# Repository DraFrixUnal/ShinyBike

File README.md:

# Shiny Bike

Dispositivo que busca iluminar y señalizar a las bicicletas.

## Descripcion

Este dispositivo busca que los ciclistas puedan señalizar a traves de luces su recorrido en las calles (direccionales, frenado, parqueo). El dispositivo se divide en dos partes, la primera la cual es un control remoto permite al usuario emitir comandos manueales y comandos automaticos para el seña.amiento, segun que comando dicte se enviaran datos via Bluetooth a la segunda parte, la cual se encarga de iluminar los led RGB Ws2812b.

## Objetivos

- Desarrollar un dispositivo que sea capaz de iluminar y señalizar de forma remota a cualquier bicicleta.
- Desarrollar los esquematicos, PCB, diseños y codigos que permitan alcanzar el dispositivo y un buen aprendizaje

## Alcance

Todos los ciclistas que quieran iluminar sus aventuras en la calle.

## Planeación 

### Diagrama de Flujo

Aqui se establecio oficialmente las funciones y las interacciones del dispositivo.

### Diagrama de Cajas Negras

Aqui se establecieron las principales tecnologias.

# Diseño

En esta sección, se empieza diseñar y construir la parte electronica del dispositivo, con lo cual se diseñaron los esquematicos y las PCB.

## Esquematicos

Esquematico Control Remoto

Esquematico Luces

## PCB

PCB del Control Remoto

PCB de apartado de Luces

# Prueba y Trabajo hecho

Aqui se realizaron pruebas en ProtoBoard para corroborar el funcionamiento del codigo y construir el dispositivo final.

## Videos

Links de los videos:
 - Dispositivo funcionamiento [Vdf](https://youtu.be/l_CRdRnh4ok)
 - Explicacion Bluetooth [Veb](https://youtu.be/JUIpYABRpQY)
 - Videos de los problemas [Vp1](https://youtu.be/4-EyFK3v-QM),[Vp2](https://youtube.com/shorts/PcfQB73DB2A?feature=share),[Vp3](https://youtu.be/3R93eb1QBnk)

## Muchas gracias por su visita

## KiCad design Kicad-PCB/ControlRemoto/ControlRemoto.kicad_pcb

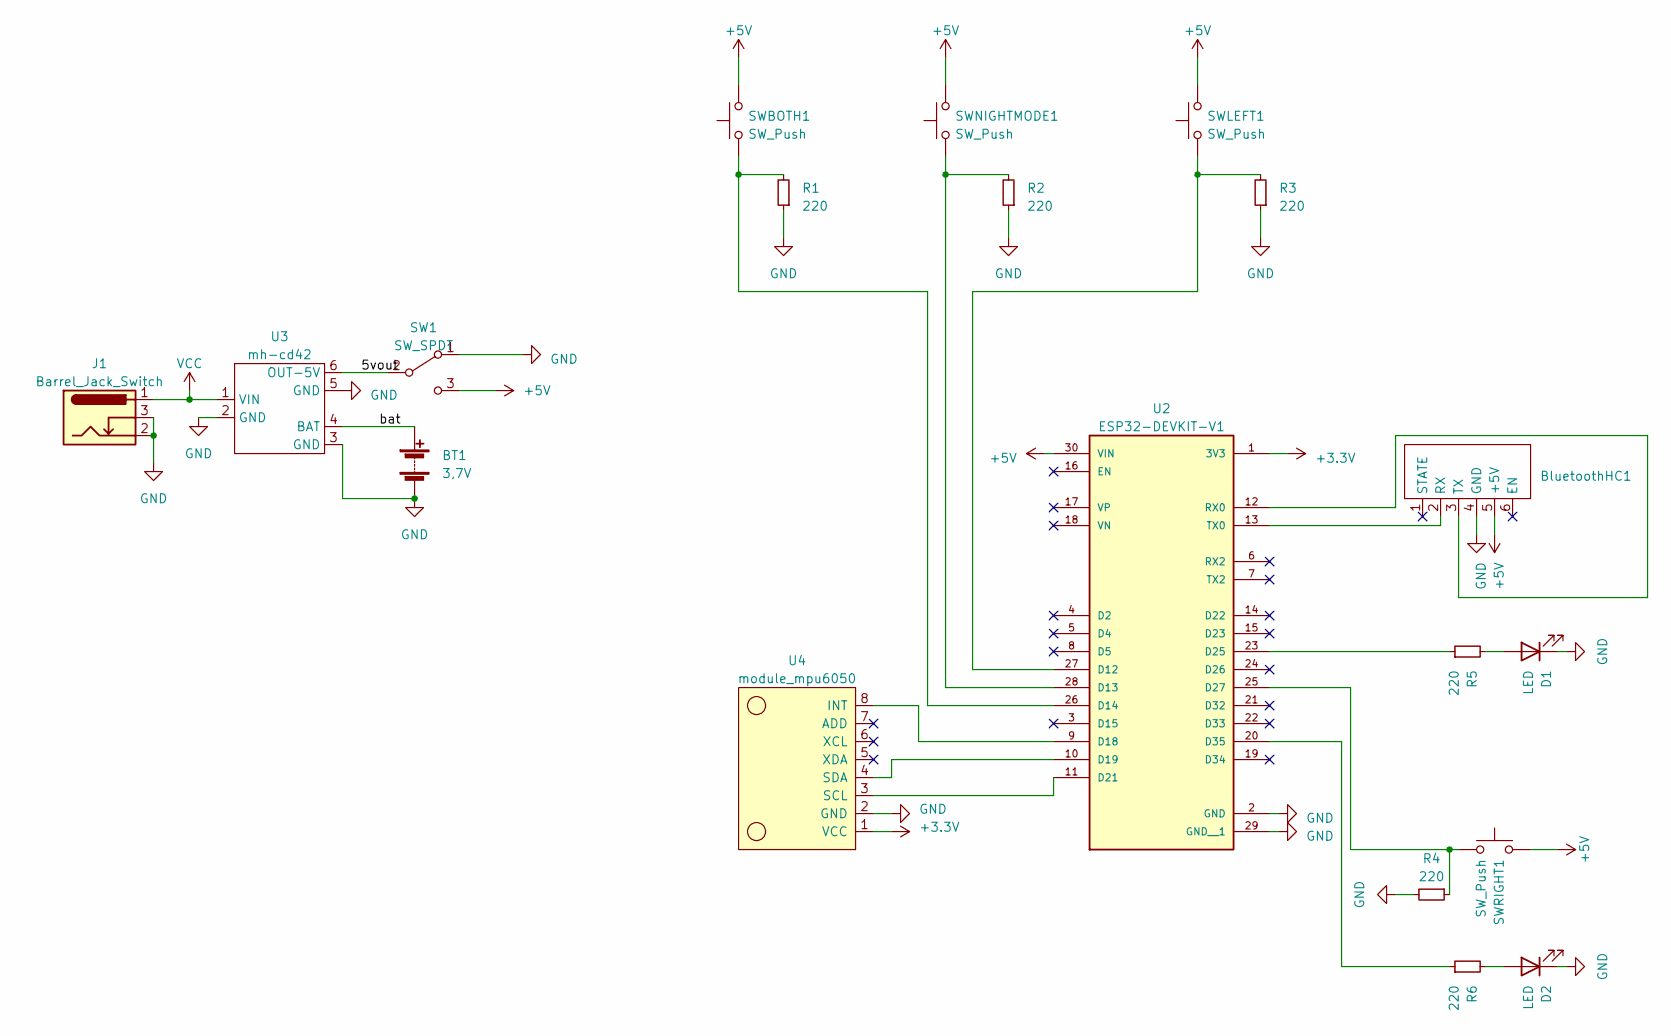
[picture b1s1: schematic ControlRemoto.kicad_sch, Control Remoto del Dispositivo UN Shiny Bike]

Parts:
BT1: 3,7V; SolderWire-0.1sqmm_1x02_P3.6mm_D0.4mm_OD1mm
BluetoothHC1: hc-05
D1, D2: LED; LED_D4.0mm
J1: Barrel_Jack_Switch; BarrelJack_Horizontal
R1, R2, R3, R4, R5, R6: 220; R_Axial_DIN0207_L6.3mm_D2.5mm_P7.62mm_Horizontal
SW1: SW_SPDT; SolderWire-0.1sqmm_1x03_P3.6mm_D0.4mm_OD1mm
SWBOTH1: SW_Push; SW_PUSH-12mm
SWLEFT1: SW_Push; SW_PUSH-12mm
SWNIGHTMODE1: SW_Push; SW_PUSH-12mm
SWRIGHT1: SW_Push; SW_PUSH-12mm
U2: ESP32-DEVKIT-V1; MODULE_ESP32_DEVKIT_V1; PARTREV N/A
U3: mh-cd42
U4: module_mpu6050

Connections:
+3.3V: U2.1 (3V3), U4.1 (VCC)
+5V: BluetoothHC1.5 (+5V), SW1.3 (C), SWBOTH1.2, SWLEFT1.2, SWNIGHTMODE1.2, SWRIGHT1.2, U2.30 (VIN)
/5vout: SW1.2 (B), U3.6 (OUT-5V)
/bat: BT1.1 (+), U3.4 (BAT)
GND: BT1.2 (-), BluetoothHC1.4 (GND), D1.1 (K), D2.1 (K), J1.2, J1.3, R1.1, R2.1, R3.1, R4.2, SW1.1 (A), U2.2 (GND), U2.29 (GND__1), U3.2 (GND), U3.3 (GND), U3.5 (GND), U4.2 (GND)
unnamed: BluetoothHC1.2 (RX), U2.13 (TX0)
unnamed: BluetoothHC1.3 (TX), U2.12 (RX0)
unnamed: D1.2 (A), R5.2
unnamed: D2.2 (A), R6.2
unnamed: R3.2, SWLEFT1.1, U2.27 (D12)
unnamed: R2.2, SWNIGHTMODE1.1, U2.28 (D13)
unnamed: R1.2, SWBOTH1.1, U2.26 (D14)
unnamed: U2.9 (D18), U4.8 (INT)
unnamed: U2.10 (D19), U4.4 (SDA)
unnamed: U2.11 (D21), U4.3 (SCL)
unnamed: R5.1, U2.23 (D25)
unnamed: R4.1, SWRIGHT1.1, U2.25 (D27)
unnamed: R6.1, U2.20 (D35)
VCC: J1.1, U3.1 (VIN)

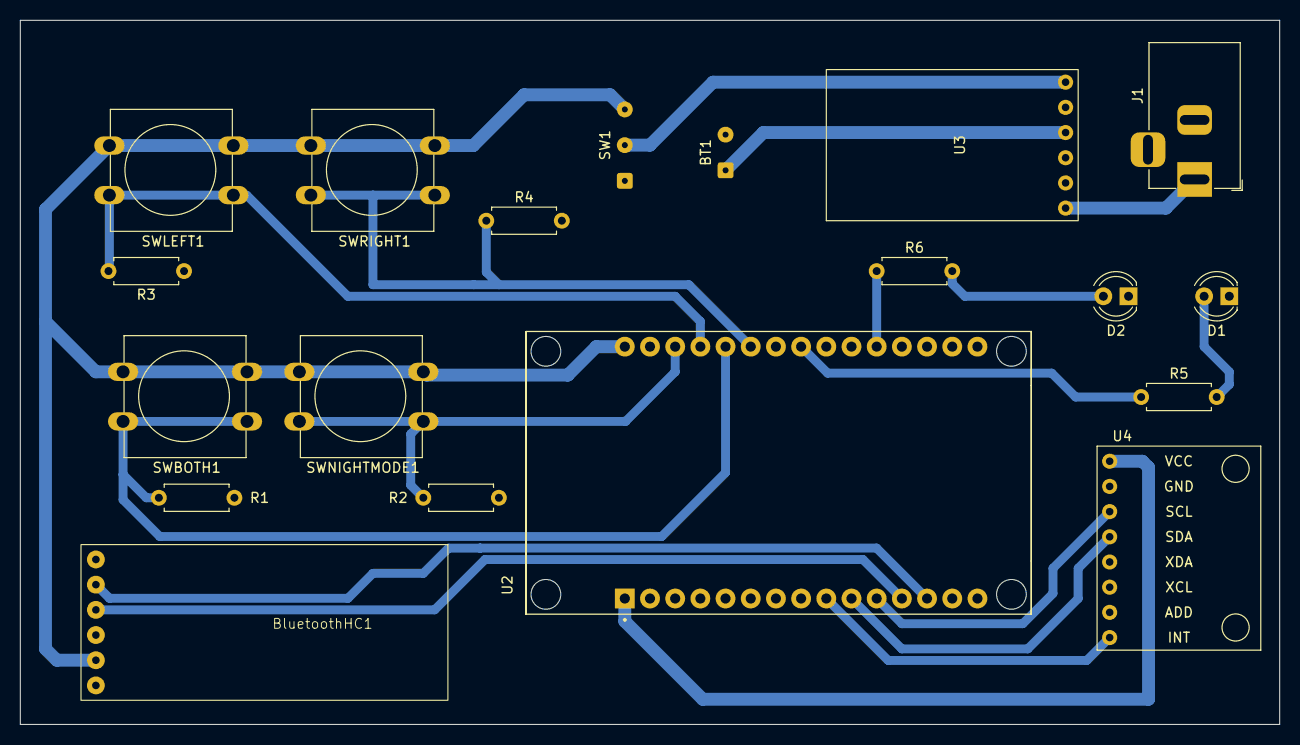
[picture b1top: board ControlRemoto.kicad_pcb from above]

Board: 2 copper layers, 127.0 x 71.0 mm, 19 parts (0 on the bottom side), 19 nets.

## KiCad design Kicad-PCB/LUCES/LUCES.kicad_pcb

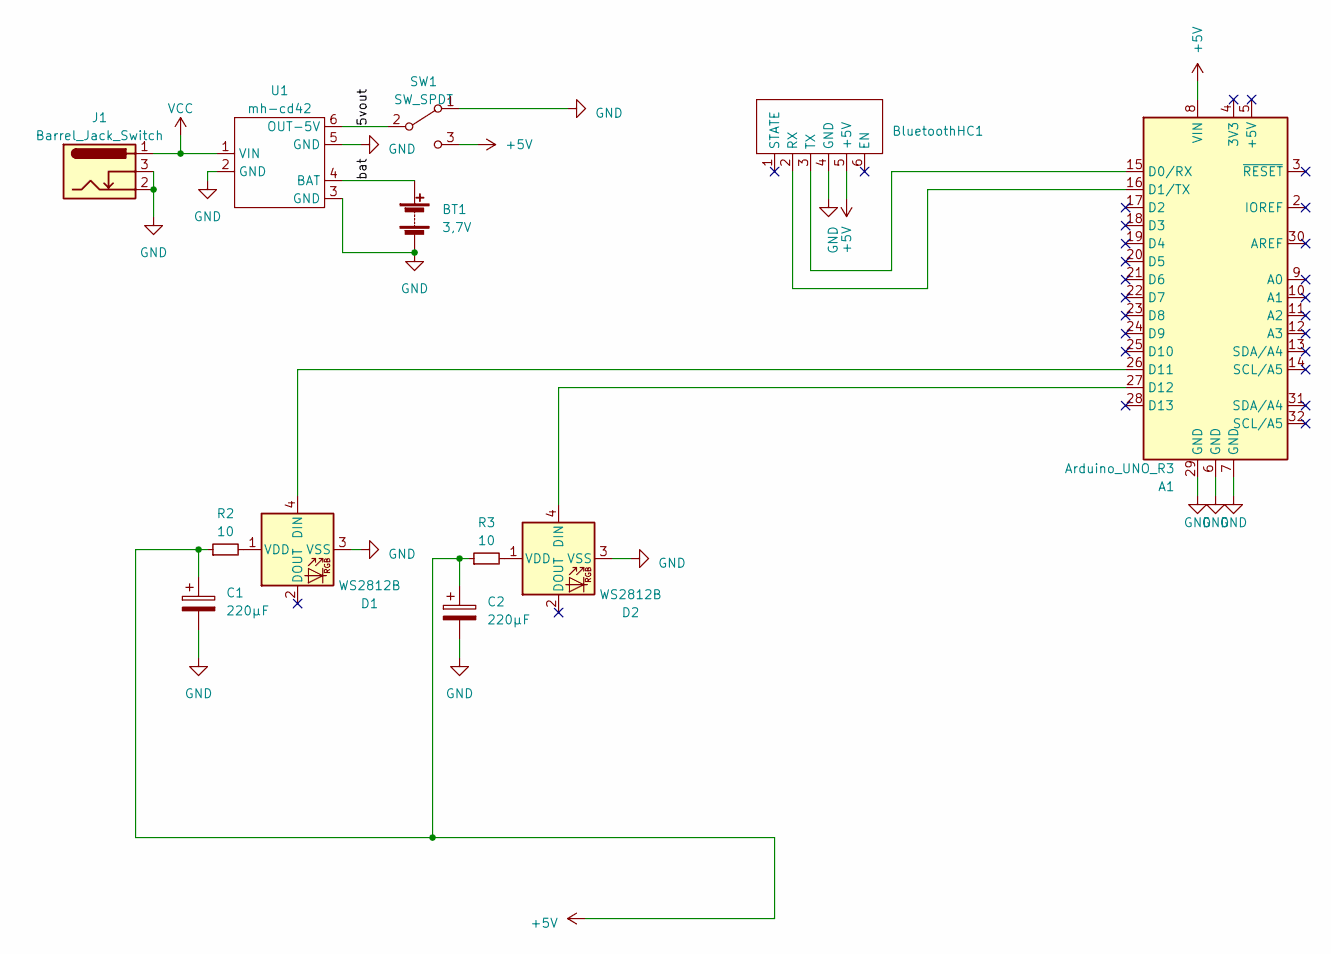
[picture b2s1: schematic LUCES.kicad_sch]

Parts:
A1: Arduino_UNO_R3
BT1: 3,7V; SolderWire-0.1sqmm_1x02_P3.6mm_D0.4mm_OD1mm
BluetoothHC1: hc-05
C1, C2: 220µF; CP_Radial_D5.0mm_P2.00mm
D1, D2: WS2812B; SolderWire-0.1sqmm_1x04_P3.6mm_D0.4mm_OD1mm
J1: Barrel_Jack_Switch; BarrelJack_Horizontal
R2, R3: 10; R_Axial_DIN0204_L3.6mm_D1.6mm_P5.08mm_Horizontal
SW1: SW_SPDT; SolderWire-0.1sqmm_1x03_P3.6mm_D0.4mm_OD1mm
U1: mh-cd42

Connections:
+5V: A1.8 (VIN), BluetoothHC1.5 (+5V), C1.1, C2.1, R2.1, R3.1, SW1.3 (C)
/5vout: SW1.2 (B), U1.6 (OUT-5V)
/bat: BT1.1 (+), U1.4 (BAT)
GND: A1.6 (GND), A1.7 (GND), A1.29 (GND), BT1.2 (-), BluetoothHC1.4 (GND), C1.2, C2.2, D1.3 (VSS), D2.3 (VSS), J1.2, J1.3, SW1.1 (A), U1.2 (GND), U1.3 (GND), U1.5 (GND)
unnamed: A1.15 (D0/RX), BluetoothHC1.3 (TX)
unnamed: A1.16 (D1/TX), BluetoothHC1.2 (RX)
unnamed: A1.26 (D11), D1.4 (DIN)
unnamed: A1.27 (D12), D2.4 (DIN)
unnamed: D1.1 (VDD), R2.2
unnamed: D2.1 (VDD), R3.2
VCC: J1.1, U1.1 (VIN)

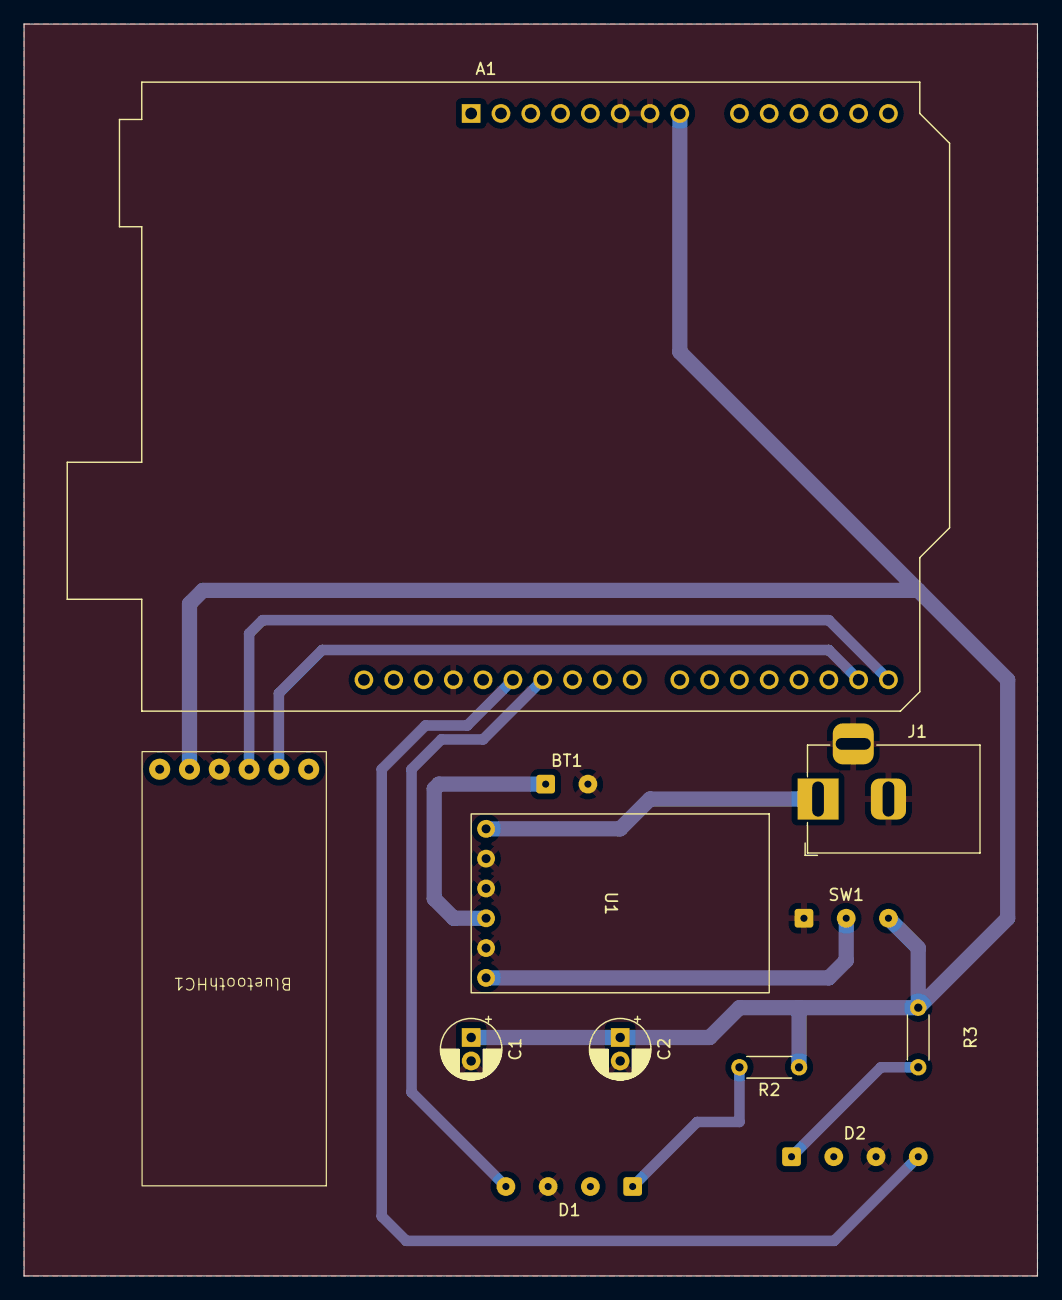
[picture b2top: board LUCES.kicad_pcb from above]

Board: 2 copper layers, 86.4 x 106.7 mm, 12 parts (0 on the bottom side), 11 nets.

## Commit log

2023-06-27 Primer commit, code, diagramas, pcb, etc
2023-06-28 documentacion
2023-06-28 readme
2023-06-28 holiwis
2023-06-28 holiwis2
2023-06-28 holiwis3
